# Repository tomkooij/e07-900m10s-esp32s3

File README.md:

# e07-900m10s-esp32s3 adapter board for ESP32 S3 DevKit and mini boards
Adapter board for [ebyte e07-900m10s CC1101 module](https://www.ebyte.com/en/product-view-news.html?id=1567)

3d view:

This should run [Ramses_ESP](https://github.com/IndaloTech/ramses_esp/) out of the box on:

ESP32 S3 DevKit-C module (9 units wide)
(TODO link and pic)

[ESP32 S3 DevKit-C module](https://nl.aliexpress.com/item/1005006387668474.html) (10 units wide)

 - [E07 900M10S](https://www.ebyte.com/en/product-view-news.html?id=1567) cc1101 module.
 - C1 and C2 are 1206 SMD size
 - C1 = 100nF
 - C2 = 10uF
 - C2 is probably not needed, it is used as a buffer for large currents while sending.
 - LED TX blue SMD 1206
 - LED RX green SMD 1206
 - THT LEDs as backup.
 - Suitable value for R1-R4 is about 1k ohms. I tried 220 ohm but is was too bright.
 - Antenna connector is [PCB SMA female](https://nl.aliexpress.com/item/1005005708712726.html) (use standard 1.6mm board thickness)
 - Antenna is a male SMA 3dBi 868/915Mhz 5cm antenna. This [TX-915-XPL-100 antenna](https://nl.aliexpress.com/item/1005004843392517.html) works great.
 - The IPEX stamp antenna on the module should also be useable (not tested)
 - The header is a standard .1" (2.54mm) PCB header. It is not needed, just for testing.

This repo contains the KiCad 8 files as well as the gerbers to produce the PCB.
I used JLCPCB for my board. Just upload the zip-file in the gerber folder to JLPCB.

## Known issues (improvements)
 - Messed up the ESP32C3 supermini pinout. Jumper/botch wires necessary.
 - Mounting holes not 100% square
 - Mounting hole H1 is in ESP32S3 Antenna keep out zone
 - Pin markings on back of PCB (for soldering) would be nice
 - GND fill on entire top layer

## Prototype:

This is a clone of the (excellent!) [Ramses_ESP](https://github.com/IndaloTech/ramses_esp/) Ramses-II RF bridge. (evofw3 HGI-80 clone).
Using the esp32-s3 it clones the behaviour of the HGI-80: RF tot USB serial and adds MQTT over WiFi.

## Pinouts
The PCB uses the Ramses ESP pinouts:

 - pin 35: MOSI
 - pin 36: SCL
 - pin 37: MISO
 - pin 38: CSN
 - pin 39: GDO0
 - pin 40: GDO2

optional:
 - pin 41: RX
 - pin 42: TX

On DevKit C board pin 0 is connected to the BOOT button, which is the Ramses ESP option button.

## Other ESP32 boards
[Waveshare ESP32 s3 zero](https://www.waveshare.com/esp32-s3-zero.htm) 

Mount the ESP32 s3 mini as shown.
Close S3_3V3 and S3_GND solder bridges.
```
idf.py menuconfig
 Partition Table (Single factory app (large), no OTA) 
CC1011 pins 1-6 instead of 35-40 (MOST-GDO2)
```
Optionally connect RX and TX to other pins and configure in `idf.py menuconfig`

[ESP32 c3 mini board](https://nl.aliexpress.com/i/1005005319963906.html)

Mount the ESP32 C3 mini board with pin 21 at "GDO2" (pin40 on esp32s3 devkit C).
On the side of the USB connector one hole on the PCB is not used.
Close the C3_3V3 and C3_GND solderbridges.

Note that the C3 is a single-core RISC-V board. It may not run Ramses_ESP correctly. (Perhaps turn wifi/mqtt off).

## Where can I order?
Buy the original ramses ESP from [IndaloTech](https://indalo-tech.onlineweb.shop/). This product is not affialiated at all with IndaloTech. It's just a clone. However, I've previously bought a SSM-D2 (ramses_esp predecessor) and its build quality is excellent.

You can order the PCB from your favorite PCB fabshop using the gerbers in the gerber folder. I used JLCPCB.

I might sell some stuff on [Tweakers V&A](https://tweakers.net/aanbod/user/90636/) (NL only)

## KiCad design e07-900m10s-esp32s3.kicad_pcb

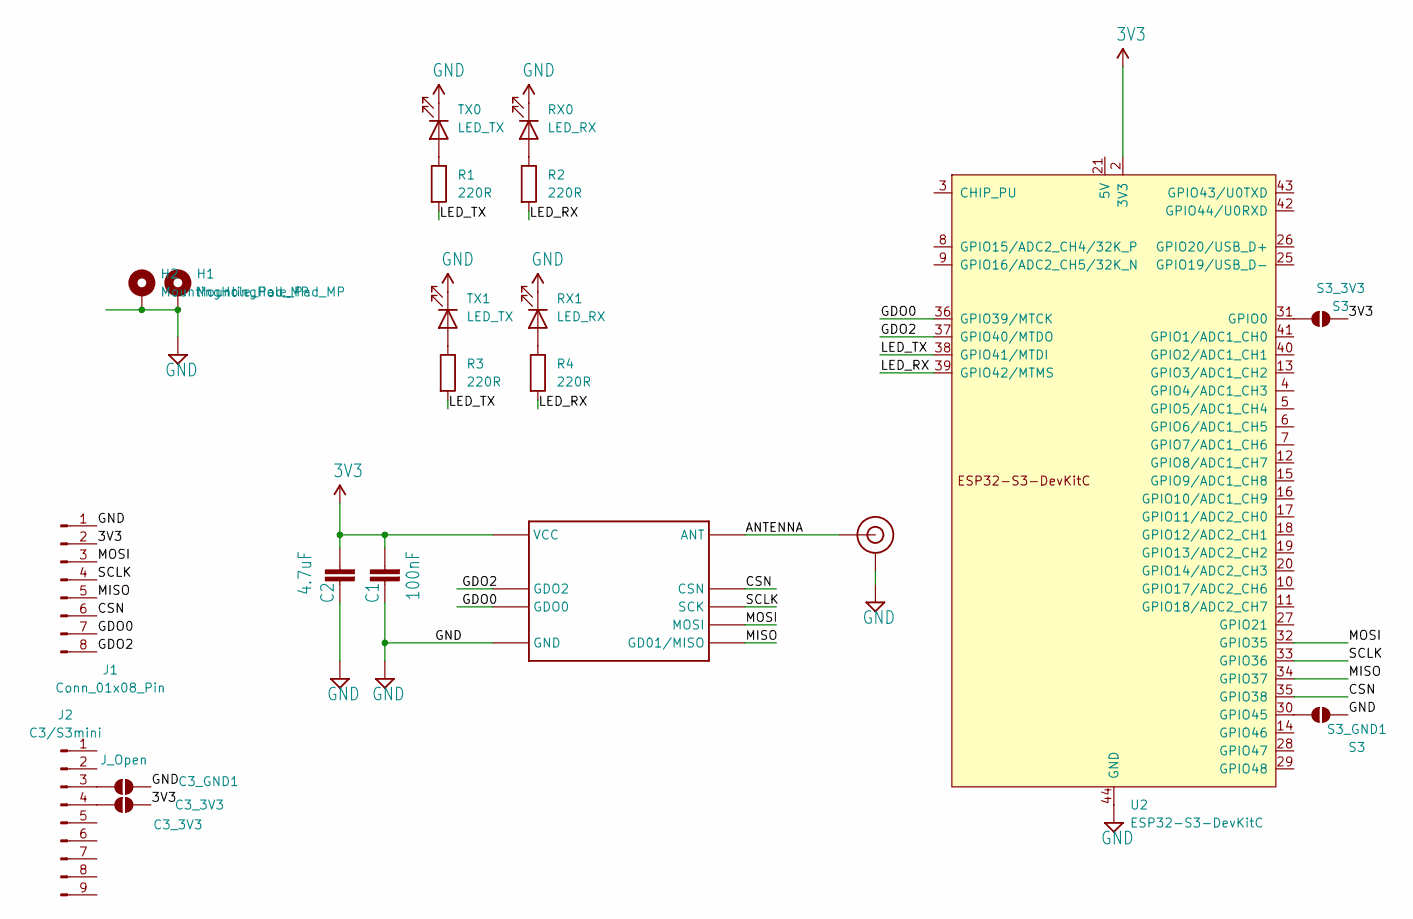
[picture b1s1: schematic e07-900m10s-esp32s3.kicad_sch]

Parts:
C1: 100nF; C_1210_3225Metric_Pad1.33x2.70mm_HandSolder
C2: 4.7uF; C_1210_3225Metric_Pad1.33x2.70mm_HandSolder
C3_3V3: C3_3V3; SolderJumper-2_P1.3mm_Open_TrianglePad1.0x1.5mm
C3_GND1: J_Open; SolderJumper-2_P1.3mm_Open_TrianglePad1.0x1.5mm
H1, H2: MountingHole_Pad_MP; MountingHole_2.5mm_Pad_Via
J1: Conn_01x08_Pin; PinHeader_1x08_P2.54mm_Vertical
J2: C3/S3mini; PinSocket_1x09_P2.54mm_Vertical
J$1: ANTENNASMA; SMA_PAD
R1, R2: 220R; R_Axial_DIN0411_L9.9mm_D3.6mm_P12.70mm_Horizontal
R3, R4: 220R; R_1206_3216Metric_Pad1.30x1.75mm_HandSolder
RX0: LED_RX; LED_D4.0mm
RX1: LED_RX; LED_1206_3216Metric_Pad1.42x1.75mm_HandSolder
S3_3V3, S3_GND1: S3; SolderJumper-2_P1.3mm_Open_TrianglePad1.0x1.5mm
TX0: LED_TX; LED_D4.0mm
TX1: LED_TX; LED_1206_3216Metric_Pad1.42x1.75mm_HandSolder
U1: E07-900M10S
U2: ESP32-S3-DevKitC

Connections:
3V3: C1.2, C2.2, C3_3V3.2 (B), J1.2, S3_3V3.2 (B), U1.9 (VCC), U2.1 (3V3), U2.2 (3V3)
/ANTENNA: J$1.ANT0 (ANT), J$1.ANT1 (ANT), J$1.ANT2 (ANT), U1.21 (ANT)
/CSN: J1.6, U1.19 (CSN), U2.35 (GPIO38)
/GDO0: J1.7, U1.15 (GDO0), U2.36 (GPIO39/MTCK)
/GDO2: J1.8, U1.14 (GDO2), U2.37 (GPIO40/MTDO)
/LED_RX: R2.2, R4.2, U2.39 (GPIO42/MTMS)
/LED_TX: R1.2, R3.2, U2.38 (GPIO41/MTDI)
/MISO: J1.5, U1.16 (GD01/MISO), U2.34 (GPIO37)
/MOSI: J1.3, U1.17 (MOSI), U2.32 (GPIO35)
/SCLK: J1.4, U1.18 (SCK), U2.33 (GPIO36)
GND: C1.1, C2.1, C3_GND1.2 (B), H1.MP, H2.MP, J1.1, J$1.GND3 (GND), J$1.GND4 (GND), J$1.GND5 (GND), J$1.GND6 (GND), RX0.1 (K), RX1.1 (K), S3_GND1.2 (B), TX0.1 (K), TX1.1 (K), U1.1 (GND), U1.2 (GND), U1.3 (GND), U1.4 (GND), U1.5 (GND), U1.11 (GND), U1.12 (GND), U1.20 (GND), U1.22 (GND), U2.22 (GND), U2.23 (GND), U2.24 (GND), U2.44 (GND)
unnamed: C3_3V3.1 (A), J2.4
unnamed: C3_GND1.1 (A), J2.3
unnamed: R2.1, RX0.2 (A)
unnamed: R4.1, RX1.2 (A)
unnamed: S3_3V3.1 (A), U2.31 (GPIO0)
unnamed: S3_GND1.1 (A), U2.30 (GPIO45)
unnamed: R1.1, TX0.2 (A)
unnamed: R3.1, TX1.2 (A)

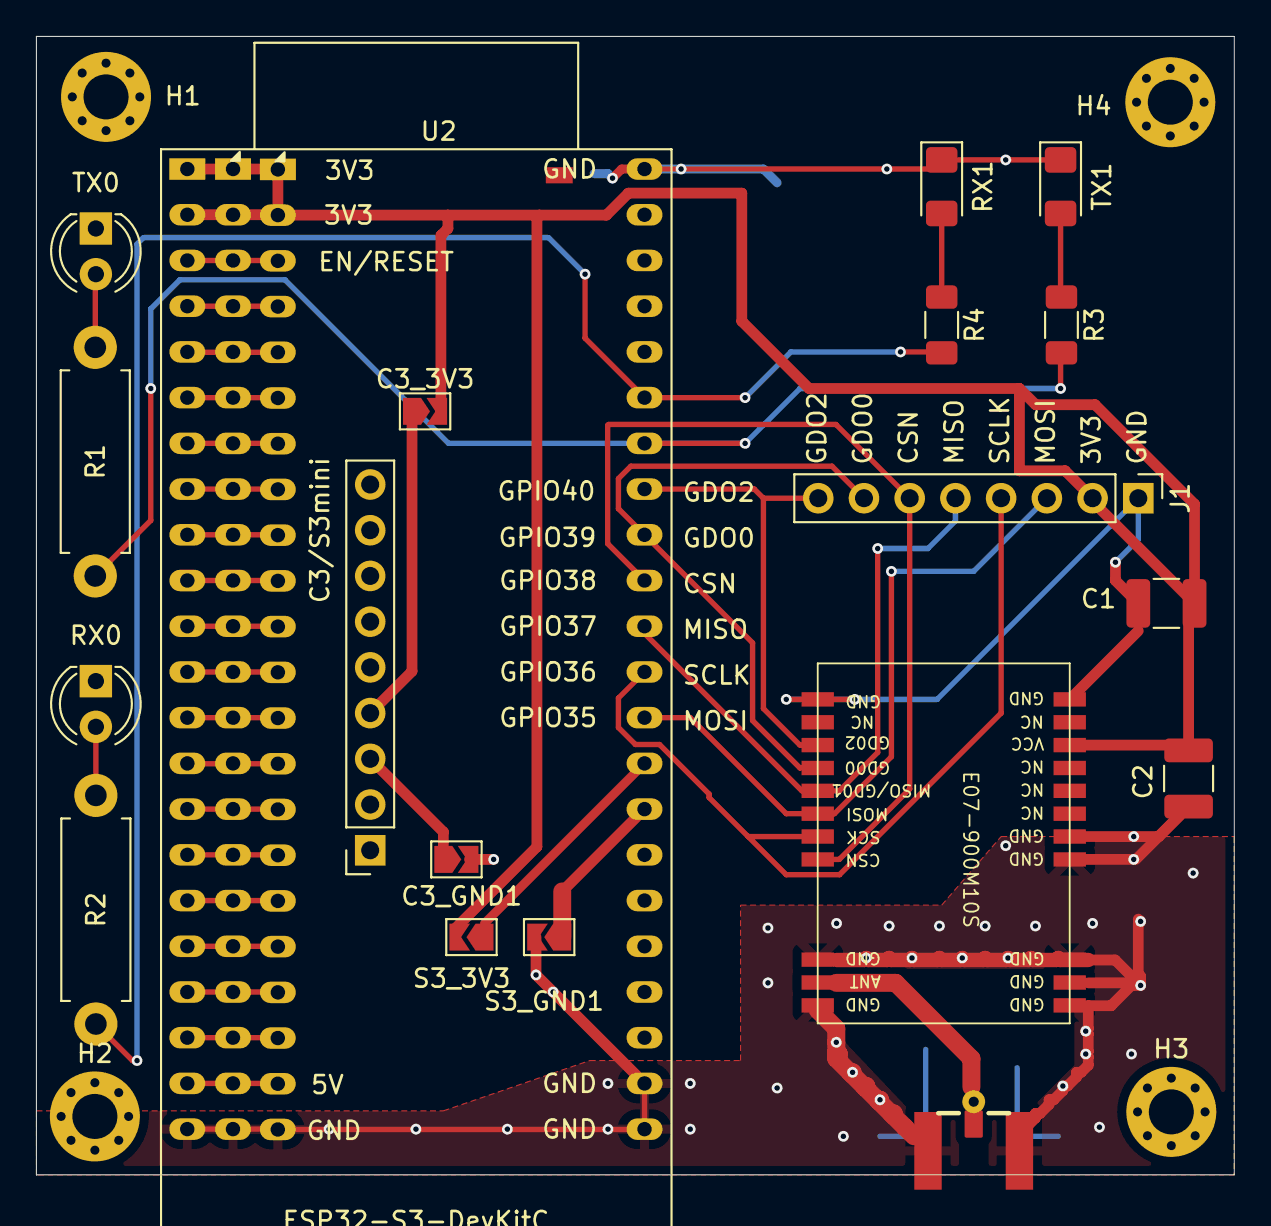
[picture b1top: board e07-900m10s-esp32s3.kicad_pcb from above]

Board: 2 copper layers, 66.5 x 63.2 mm, 23 parts (0 on the bottom side), 19 nets.

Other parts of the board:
H3, H4: MountingHole_Pad_MP; MountingHole_2.5mm_Pad_Via

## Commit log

2024-07-26 Add 3D view
2024-08-14 Update README.md
    issues/improvements
2024-08-21 Update README.md
    Suitable value for LED resistors.
